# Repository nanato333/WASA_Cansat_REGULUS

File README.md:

# WASA CanSat REGULUS

## ラジコン専用環境

`pio run -e freertos_rc -t upload --upload-port COMx` で機体へ書き込みます。
地上局PCには既存の ESP-NOW Receiver をUSB接続します。飛行の自動遷移・分離動作・ミッションNVS復元はRC環境では実行しません。

有効な電圧測定後にのみ操作でき、操作フレームが300 ms途絶えると停止して操作許可を解除します。
測定電圧が3.0 V未満の状態が200 ms続くと停止し、基板LEDが250 msごとに反転します。ロック中もテレメトリは継続します。3.3 V以上が2秒続くと再起動なしでロックを解除します。走行は自動再開せず、地上局で操作の有効化が必要です。
RCのWCPP値は `MO=3`、`AC=9` 有効化、`10` 解除・停止、`11` 前進、`12` 左、`13` 右、`14` 中立、`15` 左右独立のPWMです。`AC=15` の `DL`・`DR` はそれぞれ左・右輪の指令で、0〜30の値を後退最大〜前進最大に対応させます（15が停止）。
初回は車輪を浮かせ、指を離す・通信を切る・低電圧で停止することを確認してください。

ESP32-S3を使用するCanSat搭載ソフトウェアです。FreeRTOS版とbaremetal版があり、センサードライバー、ESP-NOW通信、WCPPテレメトリ、ミッション状態管理を共有します。

現段階ではモーター仕様が未確定のため、分離機構および走行モーターは一切駆動しません。状態4・5への遷移とサブ状態判定は行いますが、出力は安全停止のままです。

## 対象ハードウェア

- MCU: ESP32-S3-WROOM-1 N16R8
- IMU: QMI8658
- 磁気センサー: MMC5603
- 気圧センサー: HP203B
- GNSS: MAX-M10M
- 無線: ESP-NOW

ピン定義は `include/BoardConfig.h` を参照してください。

## ミッション状態

状態番号は地上局との通信仕様です。番号を変更する場合は地上局も同時に更新してください。

| 値 | 名前 | 動作 |
|---:|---|---|
| 0 | BOOT | 起動状態。地上局から開発／ミッションモードが選択されるまで待機 |
| 1 | LAUNCH_STANDBY | 打ち上げ待機。通常周期でセンサー取得とテレメトリ送信 |
| 2 | LAUNCH | 打ち上げ検知後。IMU、磁気、気圧、テレメトリを高速化 |
| 3 | DEPLOYED | ロケット放出後のパラシュート降下 |
| 4 | LANDED | 着陸後の分離フェーズ。分離機構は駆動しない |
| 5 | RUNNING | 走行フェーズ。サブ状態判定のみ行い、モーターは駆動しない |
| 6 | FINISHED | ゴール到達通知。一定時間後に状態0へ戻る |
| 7 | LOW_BATTERY | 低電圧フェイルセーフ。必要最小限のGPSテレメトリだけを低頻度送信 |

### 状態5のサブ状態

| 値 | 対応 | 名前 | 判定 |
|---:|---|---|---|
| 0 | — | NONE | 状態5以外 |
| 1 | 5a | GPS_NAVIGATION | GPSによるゴール接近 |
| 2 | 5b | RSSI_HOMING | 有効なRSSIが閾値以上 |
| 3 | 5c | STACK_ESCAPE | GPS位置、RSSI、方位が一定時間ほぼ変化しない |

5cは現在、地上局へ状態を通知して一定時間保持するだけです。脱出用モーター動作は実装していません。

## 運用モードとアップリンク

運用モードはミッション状態とは別フィールドです。

| 値 | 名前 |
|---:|---|
| 0 | UNSELECTED |
| 1 | DEVELOPMENT |
| 2 | MISSION |

地上局はWCPPコマンドの `AC` フィールドへ次の値を設定します。

| AC | コマンド |
|---:|---|
| 1 | 開発モードを選択 |
| 2 | ミッションモードを選択 |
| 3 | 状態1から状態2へLAUNCH |
| 4 | Low Battery解除条件成立後、状態7から状態0へ戻る |
| 5 | 飛行中再起動後、着地確認済みとして状態7から状態4へ復帰 |

コマンド値は MissionCommand enumで定義されています。モード選択は状態0でだけ受け付けます。ミッションモードを選択すると状態1へ遷移します。状態1では AC=3 を受けると状態2へ進みます。また、地上局コマンドが届かない場合に備え、合成加速度15 m/s²以上が300 ms継続した場合も自動的に状態2へ遷移します。開発モードでは状態0を維持します。

`AC=5` は `FAILSAFE / UNSAFE_FLIGHT_RESTART` かつミッションモードの場合だけ受理します。落下中に送ると状態4扱いになるため、地上局オペレーターが実際の着地を確認してから二段階操作で送信します。Low BatteryまたはSensor Failureによる状態7では拒否します。

## WCPPテレメトリ

パケットIDは2、コンポーネントIDは0です。

ミッション管理に関係するフィールド：

| フィールド | 内容 |
|---|---|
| `ST` | ミッション状態 0～7 |
| `SS` | 走行サブ状態 0～3 |
| `MO` | 運用モード 0～2 |
| `TI` | 起動後時刻 [s] |
| `LA`, `LO` | 緯度・経度 |
| `SA` | 捕捉衛星数 |

通常パケットには気圧、温度、IMU、磁気、姿勢、有効フラグも含まれます。状態7では時刻、状態、サブ状態、モード、GPS、衛星数だけを送信します。

## 状態遷移

FreeRTOS版とbaremetal版はともに `MissionController` を使用します。

主な自動判定：

1. 状態1で合成加速度が閾値を一定時間超えると状態2
2. 状態2で最短時間経過後、自由落下相当の加速度を検知すると状態3
3. 状態3で鉛直速度、加速度、角速度が一定時間安定すると状態4
4. 状態4で安全待機後、モーターを停止したまま状態5
5. 状態5で設定済みゴール座標の範囲内に一定時間留まると状態6
6. 状態6の通知時間経過後、運用モードを未選択に戻して状態0
7. 有効なバッテリー電圧が低電圧閾値以下で継続すると状態7

バッテリー電圧が0 V、NaN、未計測の場合は状態7へ遷移しません。

## ゴール座標の設定

誤った座標でミッション終了しないよう、デフォルトではゴール判定を無効にしています。実機用ビルドフラグへ次を追加すると有効になります。

```ini
build_flags =
    ${env.build_flags}
    -D MISSION_GOAL_LATITUDE=35.000000
    -D MISSION_GOAL_LONGITUDE=139.000000
```

座標を設定しない場合も、状態5のGPS／RSSI／スタック判定は継続しますが、状態6へは自動遷移しません。

## バッテリー電圧とRSSI

`update_system_status(float battery_voltage, int rssi)` で共有データへ入力します。

- バッテリー電圧: V単位。0以下は未計測扱い
- RSSI: dBm単位の負値。0以上は未計測扱い

現在の基板入力処理にはバッテリーADC取得がまだ接続されていません。また、使用中のArduino ESP32 2.xのESP-NOW受信コールバックからRSSIを取得する処理も未接続です。このため5b・5cは有効なRSSIが入力されるまで誤発動しません。

## NVS復元

- 運用モードは選択時に保存
- ミッション状態は状態遷移時だけ保存
- センサー更新周期ごとのNVS書き込みは行わない
- 状態0、1、4、5、6、7は再起動後に復元可能
- 飛行中の状態2、3から再起動した場合は、安全側として状態7へ移行
- 飛行中再起動の状態7は自動解除せず、着地確認後の `AC=5` だけで状態4へ復帰
- Low Batteryの状態7は電圧回復条件成立後の `AC=4` で状態0へ戻る

走行サブ状態は保存せず、状態5の再開時にセンサー値から再判定します。

## ビルド

PlatformIOを使用します。

```powershell
pio run -e freertos_sensors
pio run -e freertos_flight
pio run -e baremetal
pio run -e baremetal_espnow
```

| 環境 | 内容 |
|---|---|
| `freertos_sensors` | FreeRTOS、実センサー、ESP-NOWなし |
| `freertos_flight` | FreeRTOS、実センサー、ESP-NOWあり |
| `baremetal` | superloop、実センサー、ESP-NOWなし |
| `baremetal_espnow` | superloop、実センサー、ESP-NOWあり |

bring-up用に i2c_scan、imu_test、mag_test、baro_test、gnss_test、motor_test も定義されています。通常ファームウェアからモーターテストは参照されません。

### flight_mockの状態遷移試験

NVSを消去して freertos_flight_mock を書き込み、地上局から AC=2 でミッションモードを選択すると状態1になります。状態1で AC=3 を送ると直ちに状態2へ進みます。手動LAUNCHを送らない場合は、10秒後にmockが打上げ加速度を生成して自動判定経路を試験します。その後は上昇、放出、パラシュート降下、着陸を模擬して状態5まで進みます。

## ディレクトリ構成

- `include/MissionState.h`: 状態、サブ状態、モード、コマンドの通信値
- `include/MissionConfig.h`: 遷移閾値と周期
- `src/MissionController.cpp`: FreeRTOS／baremetal共通状態機械
- `src/tasks/`: FreeRTOSタスク
- `src/baremetal/main.cpp`: baremetal superloop
- `src/communication/`: ESP-NOWとWCPP
- `src/drivers/`: センサードライバー
- `src/CanSatData.cpp`: タスク／superloop間の共有データ

## 未完了・実機確認待ち

- バッテリーADC回路に合わせた電圧取得と換算
- ESP-NOW受信RSSIの取得方法確定と共有データへの接続
- ゴール座標、ゴール半径、RSSI閾値、スタック判定値の実験調整
- パラシュート分離機構
- GPS走行、RSSIホーミング、スタック脱出のモーター制御
- 基板上でのESP-NOW送受信確認
- 実飛行ログに基づく打ち上げ・放出・着陸閾値の再調整

## ESP-NOW受信機を基板へ書き込む

ESP-NOWチャンネルは1、USBシリアルは115200 baud、受信表示LEDはGPIO21です。

ビルド：

    pio run -e espnow_receiver

自動検出したポートへ書き込み：

    pio run -e espnow_receiver -t upload

複数のESP32が接続されている場合は、先にポートを確認して明示します。

    pio device list
    pio run -e espnow_receiver -t upload --upload-port COM5

ReceiverはUSBへWCPPバイナリを直接出力します。地上局を起動している間は同じCOMポートをPlatformIOのシリアルモニターで同時に開かないでください。
## Goal navigation and motor sequence

The ground station sends WCPP action `AC=6` with Float64 `GL` (latitude) and `GO` (longitude). The vehicle validates the coordinate, stores it in ESP32 NVS, and echoes `GC`, `GL`, `GO`, `GD`, `MC`, and `PS` in normal telemetry.

State 4 writes the separation-attempt flag to NVS before driving both TB6612FNG channels forward for 10 seconds. A reboot never repeats an attempted separation; it resumes at State 5 with `PS=2` (complete) or `PS=3` (aborted). State 5 stops unless the goal, GNSS fix, and magnetometer heading are valid. It drives straight inside the heading deadband, turns with only the outside wheel, stops inside 5 m, confirms for 5 seconds, and enters State 6. State 7 always stops both motors.

Motor mapping is defined in `include/BoardConfig.h`. Current defaults assume motor A is the right wheel and both channels move forward with IN1 high / IN2 low. Confirm wheel assignment and polarity with the vehicle lifted before flight; change only these booleans if wiring differs.

Telemetry additions: `GC` goal configured, `GL` goal latitude, `GO` goal longitude, `GD` distance metres, `MC` motor state (`0 stop`, `1 forward`, `2 left`, `3 right`), and `PS` separation state (`0 not started`, `1 active`, `2 complete`, `3 aborted`).
## Manual phase recovery commands

WCPP `AC=7` (`CONFIRM_DEPLOYED`) is accepted only in Mission Mode while State 2 is active and advances to State 3. `AC=8` (`CONFIRM_LANDED`) is accepted in Mission Mode from State 2 or 3, or in Development Mode from State 0 for a lifted ground test. Entering State 4 immediately starts the one-time 10 second separation motor sequence. Invalid mode/state combinations are rejected by the vehicle. Flight-restart State 7 recovery continues to use `AC=5` (`RESUME_LANDED`).
### Ground receiver GNSS

The `espnow_receiver` environment now reads its onboard MAX-M10M with the same TinyGPS++ driver and board wiring as the flight unit (`RX=GPIO18`, `TX=GPIO17`, `9600 baud`). Once per second it emits a receiver-only WCPP diagnostic packet over USB containing `RL` latitude, `RO` longitude, `RA` satellites, `RV` UART validity, `RF` fix validity, and `RT` receiver time. This packet is not forwarded over ESP-NOW and does not overwrite vehicle GNSS telemetry.

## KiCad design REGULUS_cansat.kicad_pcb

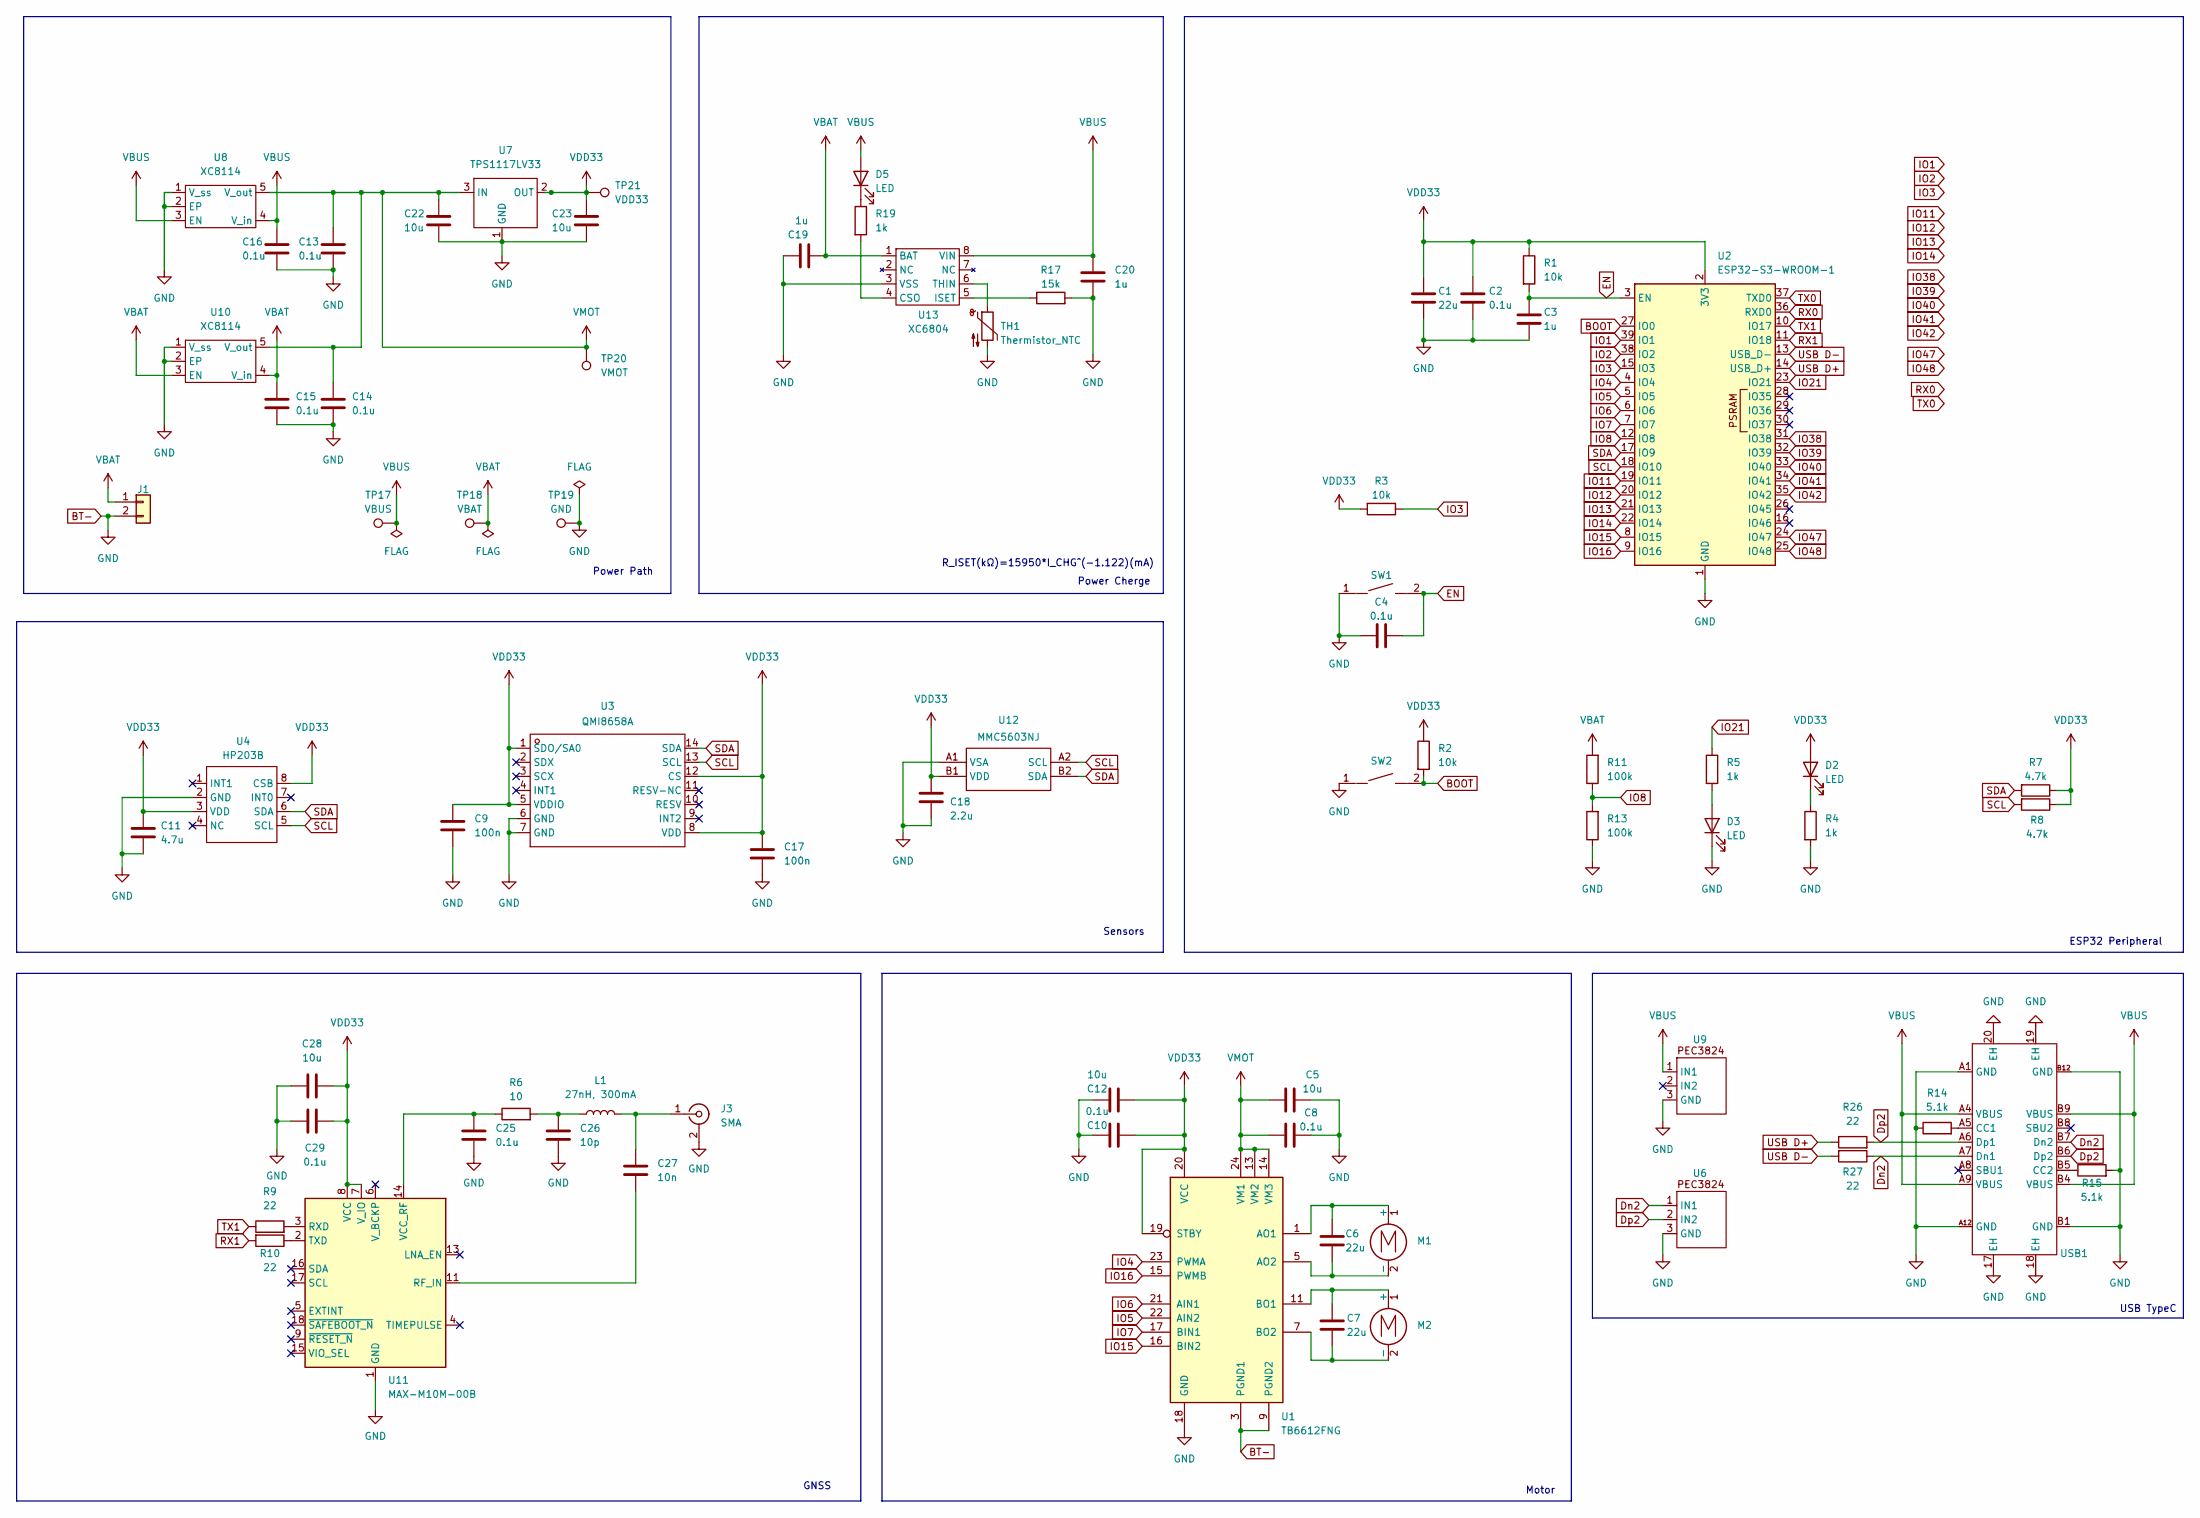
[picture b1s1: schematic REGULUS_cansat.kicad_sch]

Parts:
C1: 22u; C_0603_1608Metric
C2, C4, C8, C10, C13, C14, C15, C16: 0.1u; C_0402_1005Metric
C3, C19, C20: 1u; C_0402_1005Metric
C5, C12, C22, C23: 10u; C_0402_1005Metric
C6, C7: 22u; C_0805_2012Metric
C9, C17: 100n; C_0402_1005Metric
C11: 4.7u; C_0402_1005Metric
C18: 2.2u; C_0402_1005Metric
C25, C29: 0.1u; C_0402_1005Metric; LCSC C1525
C26: 10p; C_0402_1005Metric; LCSC C1525
C27: 10n; C_0402_1005Metric; LCSC C1525
C28: 10u; C_0402_1005Metric; LCSC C1525
D2, D3, D5: LED; LED_0603_1608Metric
J1: Conn_01x02; wire pad 1_2
J3: SMA; U.FL_Hirose_U.FL-R-SMT-1_Vertical; LCSC C2693813
L1: 27nH, 300mA; L_0402_1005Metric; LCSC C18830
M1, M2: Motor_DC; wire pad 1_2
R1, R2, R3: 10k; R_0402_1005Metric
R4, R5, R19: 1k; R_0402_1005Metric
R6: 10; R_0402_1005Metric; LCSC C25077
R7, R8: 4.7k; R_0402_1005Metric
R9, R10: 22; R_0402_1005Metric; LCSC C25077
R11, R13: 100k; R_0402_1005Metric
R14, R15: 5.1k; R_0402_1005Metric
R17: 15k; R_0402_1005Metric; LCSC C25077
R26, R27: 22; R_0402_1005Metric
SW1, SW2: SW-SMD_L3.9-W3.0-P4.45; Manufacturer Part TS-1088-AR02016; LCSC Part Name 4*3*2mm 立贴 轻触开关
TH1: Thermistor_NTC; NTC_103JT-050
TP17: VBUS; TestPoint_Pad_D2.0mm
TP18: VBAT; TestPoint_Pad_D2.0mm
TP19: GND; TestPoint_Pad_D2.0mm
TP20: VMOT; TestPoint_Pad_D2.0mm
TP21: VDD33; TestPoint_Pad_D2.0mm
U1: TB6612FNG; SSOP-24_5.3x8.2mm_P0.65mm
U2: ESP32-S3-WROOM-1
U3: LGA-14_L3.0-W2.5-P0.50-TL; Manufacturer Part QMI8658A; LCSC Part Name A档 六轴陀螺仪
U4: QFN-8_HP203B; Manufacturer Part HP203B; LCSC Part Name 高精密气压、高度传感器
U6, U9: SOT-23_Handsoldering
U7: TPS1117LV33; SOT-223-3_TabPin2
U8, U10: XC8114; SOT-89-5_Handsoldering
U11: MAX-M10M-00B; MOD18_MAX-M10M_UBL
U12: FLIPCHIP-4_L0.8-W0.8-R2-C2-P0.40-TL; Manufacturer Part MMC5603NJ; LCSC Part Name 三轴磁传感器
U13: XC6804; SOP-8_6.62x9.15mm_P2.54mm
USB1: USB-C_UC09-0B16F00P11; Manufacturer Part UC09-0B16F00P11; LCSC Part Name Type-C 母 卧贴

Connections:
BOOT: R2.2, SW2.2, U2.27 (IO0)
BT-: C1.2, C2.2, C3.2, C4.1, C5.2, C8.2, C9.2, C10.2, C11.2, C12.2, C13.2, C14.2, C15.2, C16.2, C17.2, C18.2, C19.1, C20.2, C22.2, C23.2, C25.2, C26.2, C28.1, C29.1, D3.1 (K), J1.2, J3.2 (Ext), R4.2, R13.1, R14.1, R15.2, R17.2, SW1.1, SW2.1, TH1.2, TP19.1, U1.3 (PGND1), U1.4 (PGND1), U1.9 (PGND2), U1.10 (PGND2), U1.18 (GND), U2.1 (GND), U2.40 (GND), U2.41 (GND), U3.6 (GND), U3.7 (GND), U4.2 (GND), U6.3 (GND), U7.1 (GND), U8.1 (V_ss), U8.2 (EP), U9.3 (GND), U10.1 (V_ss), U10.2 (EP), U11.1 (GND), U11.10 (GND), U11.12 (GND), U12.A1 (VSA), U13.3 (VSS), USB1.17 (EH), USB1.18 (EH), USB1.19 (EH), USB1.20 (EH), USB1.A1 (GND), USB1.A12 (GND), USB1.B1 (GND), USB1.B12 (GND); also elsewhere on the board
Dn2: R27.1, U6.1 (IN1), USB1.A7 (Dn1), USB1.B7 (Dn2)
Dp2: R26.2, U6.2 (IN2), USB1.A6 (Dp1), USB1.B6 (Dp2)
EN: C3.1, C4.2, R1.2, SW1.2, U2.3 (EN)
IO1: U2.39 (IO1)
IO2: U2.38 (IO2)
IO3: R3.1, U2.15 (IO3)
IO4: U1.23 (PWMA), U2.4 (IO4)
IO5: U1.22 (AIN2), U2.5 (IO5)
IO6: U1.21 (AIN1), U2.6 (IO6)
IO7: U1.17 (BIN1), U2.7 (IO7)
IO8: R11.1, R13.2, U2.12 (IO8)
IO11: U2.19 (IO11)
IO12: U2.20 (IO12)
IO13: U2.21 (IO13)
IO14: U2.22 (IO14)
IO15: U1.16 (BIN2), U2.8 (IO15)
IO16: U1.15 (PWMB), U2.9 (IO16)
IO21: R5.1, U2.23 (IO21)
IO38: U2.31 (IO38)
IO39: U2.32 (IO39)
IO40: U2.33 (IO40)
IO41: U2.34 (IO41)
IO42: U2.35 (IO42)
IO47: U2.24 (IO47)
IO48: U2.25 (IO48)
unnamed: C26.1, L1.1, R6.2
unnamed: D2.1 (K), R4.1
unnamed: D3.2 (A), R5.2
unnamed: D5.1 (K), R19.1
unnamed: C27.1, J3.1 (In), L1.2
unnamed: C6.1, M1.1 (+), U1.1 (AO1), U1.2 (AO1)
unnamed: C6.2, M1.2 (-), U1.5 (AO2), U1.6 (AO2)
unnamed: C7.1, M2.1 (+), U1.11 (BO1), U1.12 (BO1)
unnamed: C7.2, M2.2 (-), U1.7 (BO2), U1.8 (BO2)
unnamed: C27.2, U11.11 (RF_IN)
unnamed: R9.2, U11.3 (RXD)
unnamed: R10.1, U11.2 (TXD)
unnamed: C25.1, R6.1, U11.14 (VCC_RF)
unnamed: R19.2, U13.4 (CSO)
unnamed: R17.1, U13.5 (ISET)
unnamed: TH1.1, U13.6 (THIN)
unnamed: R14.2, USB1.A5 (CC1)
unnamed: R15.1, USB1.B5 (CC2)
RX0: U2.36 (RXD0)
RX1: R10.2, U2.11 (IO18)
SCL: R8.2, U2.18 (IO10), U3.13 (SCL), U4.5 (SCL), U12.A2 (SCL)
SDA: R7.2, U2.17 (IO9), U3.14 (SDA), U4.6 (SDA), U12.B2 (SDA)
TX0: U2.37 (TXD0)
TX1: R9.1, U2.10 (IO17)
USB D+: R26.1, U2.14 (USB_D+)
USB D-: R27.2, U2.13 (USB_D-)
VBAT: C15.1, C19.2, J1.1, R11.2, TP18.1, U10.3 (EN), U10.4 (V_in), U13.1 (BAT); also elsewhere on the board
VBUS: C16.1, C20.1, D5.2 (A), TP17.1, U8.3 (EN), U8.4 (V_in), U9.1 (IN1), U13.8 (VIN), USB1.A4 (VBUS), USB1.A9 (VBUS), USB1.B4 (VBUS), USB1.B9 (VBUS); also elsewhere on the board
VDD33: C1.1, C2.1, C9.1, C10.1, C11.1, C12.1, C17.1, C18.1, C23.1, C28.2, C29.2, D2.2 (A), R1.1, R2.1, R3.2, R7.1, R8.1, TP21.1, U1.19 (STBY), U1.20 (VCC), U2.2 (3V3), U3.1 (SDO/SA0), U3.5 (VDDIO), U3.8 (VDD), U3.12 (CS), U4.3 (VDD), U4.8 (CSB), U7.2 (OUT), U11.7 (V_IO), U11.8 (VCC), U12.B1 (VDD); also elsewhere on the board
VMOT: C5.1, C8.1, C13.1, C14.1, C22.1, TP20.1, U1.13 (VM2), U1.14 (VM3), U1.24 (VM1), U7.3 (IN), U8.5 (V_out), U10.5 (V_out); also elsewhere on the board

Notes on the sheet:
Sensors
R_ISET(kΩ)=15950*I_CHG^(-1.122)(mA)
ESP32 Peripheral
Power Cherge
Motor
Power Path
USB TypeC
GNSS

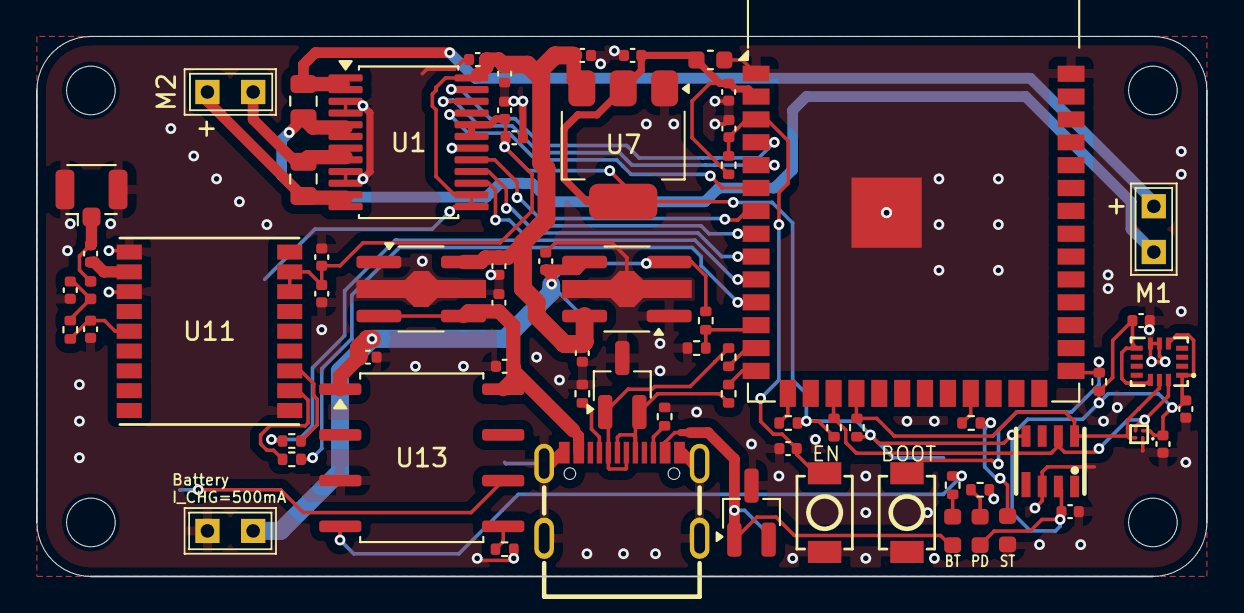
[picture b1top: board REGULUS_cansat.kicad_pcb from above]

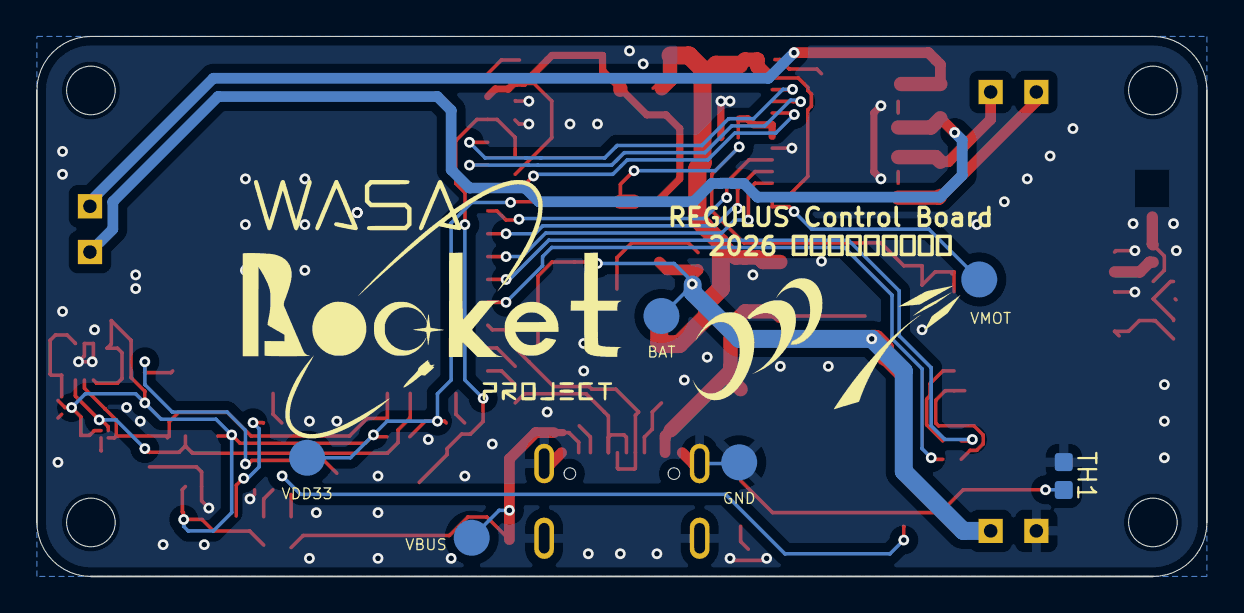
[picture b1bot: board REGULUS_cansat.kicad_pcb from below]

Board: 2 copper layers, 65.0 x 30.0 mm, 74 parts (6 on the bottom side), 42 nets.

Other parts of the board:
BAT: VBAT; TestPoint_Pad_D2.0mm
GND: GND; TestPoint_Pad_D2.0mm
VBUS: VBUS; TestPoint_Pad_D2.0mm
VDD33: VDD33; TestPoint_Pad_D2.0mm
VMOT: VMOT; TestPoint_Pad_D2.0mm

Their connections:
BT-: GND.1; also elsewhere on the board
VBAT: BAT.1; also elsewhere on the board
VBUS: VBUS.1; also elsewhere on the board
VDD33: VDD33.1; also elsewhere on the board
VMOT: VMOT.1; also elsewhere on the board
